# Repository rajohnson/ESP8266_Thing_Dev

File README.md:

SparkFun ESP8266 Thing Development Board
========================================

[*SparkFun ESP8266 Thing Development Board  (WRL-13711)*](https://www.sparkfun.com/products/13711)

The project merges the [SparkFun ESP8266 Thing Development Board](https://www.sparkfun.com/products/13711) with 5 level shifters from the [*Logic Level Converter Bi-Directional (BOB-12009)*](https://www.sparkfun.com/products/12009).

Repository Contents
-------------------

* **/Hardware** - Eagle design files (.brd, .sch)

Documentation
--------------

License Information
-------------------

This product is _**open source**_! 

Please review the LICENSE.md file for license information. 

If you have any questions or concerns on licensing, please contact techsupport@sparkfun.com.

Please use, reuse, and modify these files as you see fit. Please maintain attribution to SparkFun Electronics and release anyThing Development Board derivative under the same license.

Distributed as-is; no warranty is given.

- Your friends at SparkFun.

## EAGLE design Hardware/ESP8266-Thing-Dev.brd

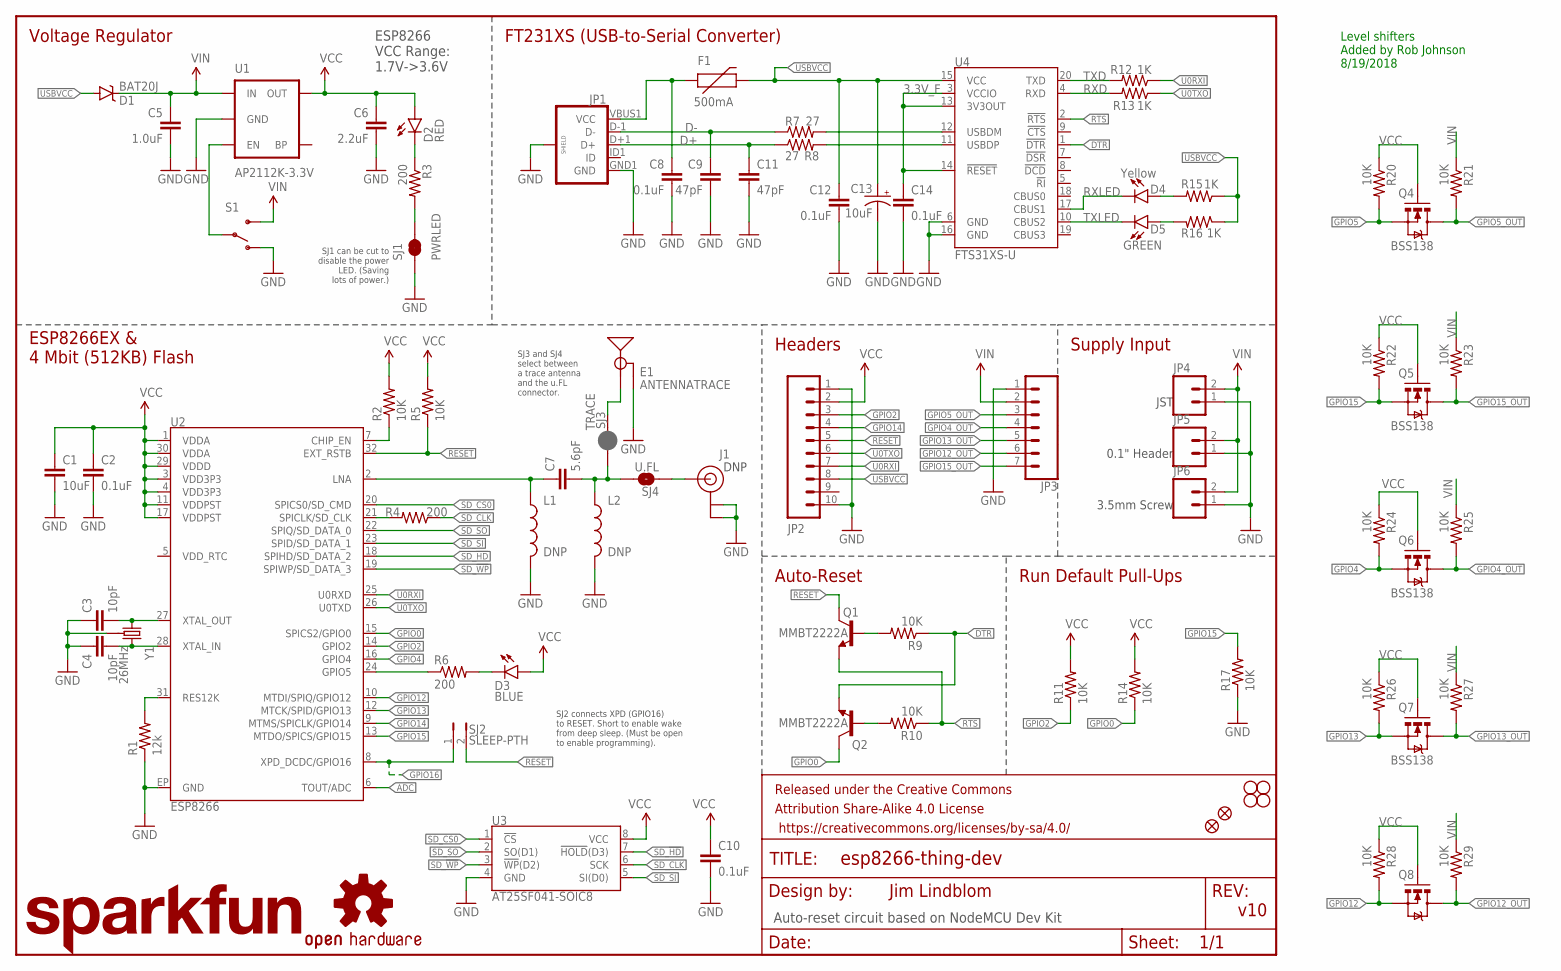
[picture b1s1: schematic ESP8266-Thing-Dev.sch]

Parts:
C1: 10uF; 0603-CAP
C2, C8, C10, C12, C14: 0.1uF; 0603-CAP
C3, C4: 10pF; 0603-CAP
C5: 1.0uF; 0805
C6: 2.2uF; 0603-CAP
C7: 5.6pF; 0603-CAP
C9, C11: 47pF; 0603-CAP
C13: 10uF; EIA3216
D1: BAT20J; SOD-323
D2: RED; LED-0603
D3: BLUE; LED-0603
D4: Yellow; LED-0603
D5: GREEN; LED-0603
E1: ANTENNATRACE; TRACE_ANTENNA_2.4GHZ_25.7MM
F1: 500mA; PTC-1206
FID1, FID2: FIDUCIAL1X2; FIDUCIAL-1X2
FRAME1: FRAME-LETTER; CREATIVE_COMMONS
J1: DNP; U.FL
JP1: USB_MICROB_PLUGCONN-11752; USB-B-MICRO-SMD_V03
JP2: M10NO_SILK_PTH_FEMALE; 1X10_NO_SILK
JP3: CONN_07NO_SILK; 1X07_NO_SILK
JP4: M02JST-PTH-2; JST-2-PTH
JP5: M021X02_NO_SILK; 1X02_NO_SILK
JP6: M023.5MM-NO_SILK; SCREWTERMINAL-3.5MM-2-NS
L1, L2: DNP; 0603
LOGO1: SFE_LOGO_NAME.2_INCH; SFE_LOGO_NAME_.2
LOGO2: OSHW-LOGOS; OSHW-LOGO-S
Q1, Q2: MMBT2222A; SOT23-3
Q4, Q5, Q6, Q7, Q8: BSS138; SOT23-3
R1: 12k; 0603-RES
R2, R5, R9, R10, R11, R14, R17, R20, R21, R22, R23, R24, R25, R26, R27, R28, R29: 10K; 0603-RES
R3, R4, R6: 200; 0603-RES
R7, R8: 27; 0603-RES
R12, R13, R15, R16: 1K; 0603-RES
S1: SWITCH-SPDT-SMD-A; SWITCH-SPST-SMD-A
SJ1: PWRLED; PAD-JUMPER-2-NC_BY_TRACE_YES_SILK
SJ2: SLEEP-PTH; PTH-JUMPER-2-NO_NO_SILK
SJ3: TRACE; PAD-JUMPER-2-NC_BY_PASTE_NO_SILK
SJ4: U.FL; PAD-JUMPER-2-NO_NO_SILK
STANDOFF1, STANDOFF2, STANDOFF3, STANDOFF4: STAND-OFF
U1: AP2112K-3.3V; SOT23-5
U2: ESP8266; QFN32
U3: AT25SF041-SOIC8; SO08
U4: FTS31XS-U; SSOP20_L
Y1: 26MHz; CRYSTAL-SMD-3.2X2.5

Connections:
3.3V_F: C14.1, U4.3 (VCCIO), U4.13 (3V3OUT), U4.14 (!RESET)
ADC: U2.6 (TOUT/ADC)
ANT: J1.P$3 (SIGNAL), SJ4.1
CHIP_EN: R2.1, U2.7 (CHIP_EN)
D+: C11.1, JP1.D+1 (D+), R8.1
D-: C9.1, JP1.D-1 (D-), R7.1
DTR: Q2.2 (E), R9.1, U4.1 (!DTR)
GND: C1.2, C2.2, C3.1, C4.1, C5.2, C6.2, C8.2, C9.2, C10.2, C11.2, C12.2, C13.C (-), C14.2, E1.GND, E1.GND2 (GND), J1.P$1 (GND), J1.P$2 (GND), JP1.GND1 (GND), JP1.SHIELD1 (SHIELD), JP1.SHIELD2 (SHIELD), JP1.SHIELD3 (SHIELD), JP2.1, JP2.10, JP3.1, JP4.1, JP5.1, JP6.1, L1.2, L2.2, R1.1, R17.1, S1.1 (O), SJ1.1, U1.2 (GND), U2.EP (GND), U3.4 (GND), U4.6 (GND), U4.16 (GND), Y1.2 (GND), Y1.4 (GND)
GPIO0: Q2.3 (C), R14.1, U2.15 (SPICS2/GPIO0)
GPIO2: JP2.3, R11.1, U2.14 (GPIO2)
GPIO4: Q6.2 (S), R24.2, U2.16 (GPIO4)
GPIO4_OUT: JP3.4, Q6.3 (D), R25.2
GPIO5: Q4.2 (S), R6.1, R20.2, U2.24 (GPIO5)
GPIO5_OUT: JP3.3, Q4.3 (D), R21.2
GPIO12: Q8.2 (S), R28.2, U2.10 (MTDI/SPIQ/GPIO12)
GPIO12_OUT: JP3.6, Q8.3 (D), R29.2
GPIO13: Q7.2 (S), R26.2, U2.12 (MTCK/SPID/GPIO13)
GPIO13_OUT: JP3.5, Q7.3 (D), R27.2
GPIO14: JP2.4, U2.9 (MTMS/SPICLK/GPIO14)
GPIO15: Q5.2 (S), R17.2, R22.2, U2.13 (MTDO/SPICS/GPIO15)
GPIO15_OUT: JP3.7, Q5.3 (D), R23.2
GPIO16: SJ2.1, U2.8 (XPD_DCDC/GPIO16)
LNA: C7.1, L1.1, U2.2 (LNA)
LNA2: C7.2, L2.1, SJ3.1, SJ4.2
unnamed: R1.2, U2.31 (RES12K)
unnamed: C4.2, U2.28 (XTAL_IN), Y1.3 (2)
unnamed: C3.2, U2.27 (XTAL_OUT), Y1.1
unnamed: R7.2, U4.12 (USBDM)
unnamed: R3.2, SJ1.2
unnamed: Q1.1 (B), R9.2
unnamed: R8.2, U4.11 (USBDP)
unnamed: D5.A, R16.2
unnamed: D3.C, R6.2
unnamed: D4.A, R15.2
unnamed: D2.C, R3.1
unnamed: Q2.1 (B), R10.2
unnamed: S1.2, U1.3 (EN)
RESET: JP2.5, Q1.3 (C), R5.1, SJ2.2, U2.32 (EXT_RSTB)
RTS: Q1.2 (E), R10.1, U4.2 (!RTS)
RXD: R13.2, U4.4 (RXD)
RXLED: D4.C, U4.17 (CBUS1)
SD_!HD!: U2.18 (SPIHD/SD_DATA_2), U3.7 (!HOLD!(D3))
SD_!WP!: U2.19 (SPIWP/SD_DATA_3), U3.3 (!WP!(D2))
SD_CLK: R4.1, U3.6 (SCK)
SD_CLK0: R4.2, U2.21 (SPICLK/SD_CLK)
SD_CS0: U2.20 (SPICS0/SD_CMD), U3.1 (!CS!)
SD_SI: U2.23 (SPID/SD_DATA_1), U3.5 (SI(D0))
SD_SO: U2.22 (SPIQ/SD_DATA_0), U3.2 (SO(D1))
TRACE_ANT: E1.ANT (SIGNAL), SJ3.2
TXD: R12.2, U4.20 (TXD)
TXLED: D5.C, U4.10 (CBUS2)
U0RXI: JP2.7, R12.1, U2.25 (U0RXD)
U0TXO: JP2.6, R13.1, U2.26 (U0TXD)
USBVCC: C12.1, C13.A (+), D1.A, F1.2, JP2.8, R15.1, R16.1, U4.15 (VCC)
VCC: C1.1, C2.1, C6.1, C10.1, D2.A, D3.A, JP2.2, Q4.1 (G), Q5.1 (G), Q6.1 (G), Q7.1 (G), Q8.1 (G), R2.2, R5.2, R11.2, R14.2, R20.1, R22.1, R24.1, R26.1, R28.1, U1.5 (OUT), U2.1 (VDDA), U2.3 (VDD3P3), U2.4 (VDD3P3), U2.11 (VDDPST), U2.17 (VDDPST), U2.29 (VDDD), U2.30 (VDDA), U3.8 (VCC)
VIN: C5.1, D1.C, JP3.2, JP4.2, JP5.2, JP6.2, R21.1, R23.1, R25.1, R27.1, R29.1, S1.3 (S), U1.1 (IN)
VUSB: C8.1, F1.1, JP1.VBUS1 (VCC)

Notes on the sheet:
ESP8266EX & 4 Mbit (512KB) Flash
ESP8266 VCC Range: 1.7V->3.6V
Voltage Regulator
FT231XS (USB-to-Serial Converter)
Headers
Auto-Reset
Supply Input
JST
0.1" Header
3.5mm Screw
Run Default Pull-Ups
SJ2 connects XPD (GPIO16) to RESET. Short to enable wake from deep sleep. (Must be open to enable programming).
SJ1 can be cut to disable the power LED. (Saving lots of power.)
Jim Lindblom
v10
DNP
Auto-reset circuit based on NodeMCU Dev Kit
SJ3 and SJ4 select between a trace antenna and the u.FL connector.
Level shifters Added by Rob Johnson 8/19/2018

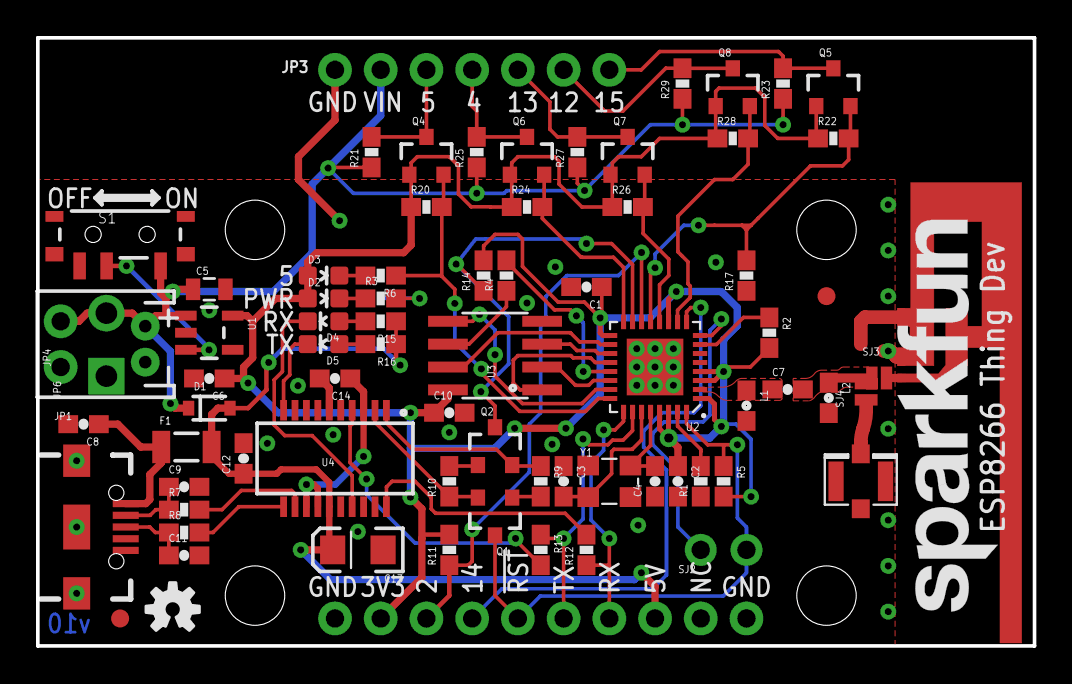
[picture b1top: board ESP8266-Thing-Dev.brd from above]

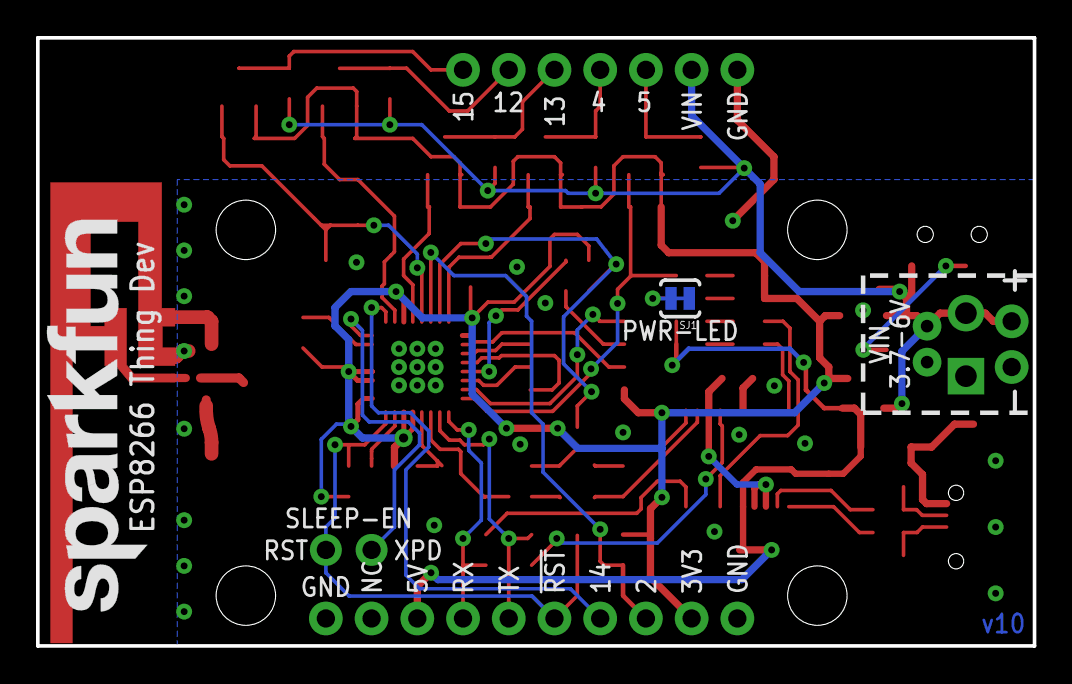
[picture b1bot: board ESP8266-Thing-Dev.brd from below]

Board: 2 copper layers, 55.4 x 33.8 mm, 84 parts (2 on the bottom side), 56 nets.

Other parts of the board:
LOGO3: SFE_LOGO_NAME.2_INCH; SFE_LOGO_NAME_.2

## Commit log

2018-08-20 Import project and add level shifters in schematic.
2018-08-20 Fix Net names for level shifter supply voltages
2018-08-20 Move level shift transistors above appropriate parts. Just a stopping point for the night.
2018-08-20 Move level shifter on GPIO 0 to GPIO 15.
2018-08-20 Switch to 7 pin header. Make board outline larger.
2018-08-21 Remove panelized PCB.
2018-08-21 Position level shifter components.
2018-08-21 Route level shifter nets and start cleaning up DRC warnings.
2018-08-22 Route last traces. Add gerbers. Clean DRC.
2018-08-22 Update gerbs.

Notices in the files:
parts and their libraries:
SparkFun-Capacitors: Licensing: Creative Commons ShareAlike 4.0 International - https://creativecommons.org/licenses/by-sa/4.0
SparkFun-Aesthetics: Released under the Creative Commons Attribution Share-Alike 4.0 License
SparkFun-Aesthetics: https://creativecommons.org/licenses/by-sa/4.0
